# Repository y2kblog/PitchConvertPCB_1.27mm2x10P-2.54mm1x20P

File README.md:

# ピッチ変換基板(1.27mm 2×10P⇔2.54mm 1×20P)

## 概要

1.27mmピッチ2×10Pを2.54mmピッチ1×20Pに変換する基板です。

## 仕様
- ピンピッチ：1.27mm 2×10P ⇔ 2.54mm 1×20P
- 基板サイズ：10mm×50.8mm
- 基板厚：1.6mm
- 基板色：緑
- 表面仕上げ：無鉛はんだ
- 両面スル―ホール
- 固定穴：45mmピッチ, M3×2穴

## 販売  
[スイッチサイエンス委託販売ページ](https://www.switch-science.com/catalog/6336/)  
※大量注文や在庫に関する問い合わせは[こちら](mailto:info.y2kb@gmail.com)までご連絡ください。  

## 寸法

## License
MIT License, see `/LICENSE`.

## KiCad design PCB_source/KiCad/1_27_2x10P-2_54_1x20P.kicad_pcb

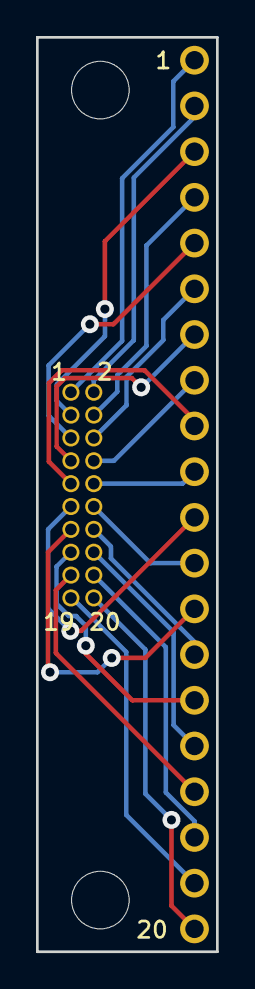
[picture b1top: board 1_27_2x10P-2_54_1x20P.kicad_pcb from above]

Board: 2 copper layers, 10.0 x 50.8 mm, 4 parts (0 on the bottom side), 20 nets.

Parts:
J1: 1.27_2x10P; USER_DILhalf_10X2_NoSilk
J2: 2.54_1x20P; USER_SIL-20_NoSilk
MH1, MH2: MountingHole; MountingHole_3.2mm_M3

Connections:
/1: J1.1, J2.1
/2: J1.2, J2.2
/3: J1.3, J2.3
/4: J1.4, J2.4
/5: J1.5, J2.5
/6: J1.6, J2.6
/7: J1.7, J2.7
/8: J1.8, J2.8
/9: J1.9, J2.9
/10: J1.10, J2.10
/11: J1.11, J2.11
/12: J1.12, J2.12
/13: J1.13, J2.13
/14: J1.14, J2.14
/15: J1.15, J2.15
/16: J1.16, J2.16
/17: J1.17, J2.17
/18: J1.18, J2.18
/19: J1.19, J2.19
/20: J1.20, J2.20

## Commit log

2020-04-14 Add prodct images
2020-05-31 add sales URL to README
